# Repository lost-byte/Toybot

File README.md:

# Toybot
Simple wheel robot with programming terminal pickaback.

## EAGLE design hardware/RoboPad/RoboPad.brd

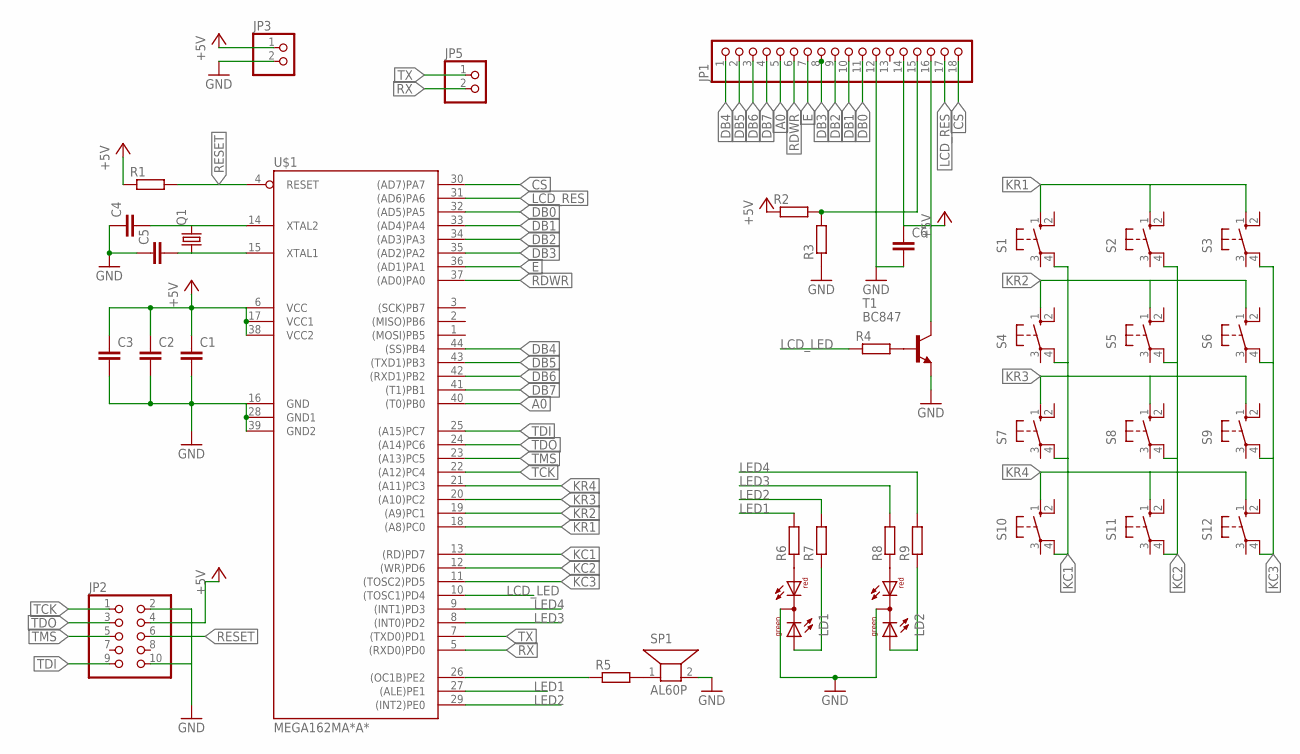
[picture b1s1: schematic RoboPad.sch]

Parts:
C1, C2, C3, C4, C5, C6: C-EUC0805; C0805
JP1: PINHD-1X18; 1X18
JP2: PINHD-2X5; 2X05
JP3, JP5: PINHD-1X2/90; 1X02/90
LD1, LD2: DUOLED-RG-C; DUOLED-C-5MM
Q1: CRYSTALHC49U-V; HC49U-V
R1, R2, R3, R4, R5, R6, R7, R8, R9: R-EU_R0805; R0805
S1, S2, S3, S4, S5, S6, S7, S8, S9, S10, S11, S12: 10-XX; B3F-10XX
SP1: AL60P
T1: BC847; SOT23
U$1: MEGA162MA*A*; TQFP44

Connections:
+5V: C1.1, C2.1, C3.1, C6.1, JP1.14, JP2.4, JP3.1, R1.1, R2.1, U$1.6 (VCC), U$1.17 (VCC1), U$1.38 (VCC2)
A0: JP1.5, U$1.40 ((T0)PB0)
CS: JP1.18, U$1.30 ((AD7)PA7)
DB0: JP1.11, U$1.32 ((AD5)PA5)
DB1: JP1.10, U$1.33 ((AD4)PA4)
DB2: JP1.9, U$1.34 ((AD3)PA3)
DB3: JP1.8, U$1.35 ((AD2)PA2)
DB4: JP1.1, U$1.44 ((SS)PB4)
DB5: JP1.2, U$1.43 ((TXD1)PB3)
DB6: JP1.3, U$1.42 ((RXD1)PB2)
DB7: JP1.4, U$1.41 ((T1)PB1)
E: JP1.7, U$1.36 ((AD1)PA1)
GND: C1.2, C2.2, C3.2, C4.1, C5.1, C6.2, JP1.12, JP2.2, JP2.10, JP3.2, LD1.C, LD2.C, R3.1, SP1.2, T1.2 (E), U$1.16 (GND), U$1.28 (GND1), U$1.39 (GND2)
KC1: S1.4 (P1), S4.4 (P1), S7.4 (P1), S10.4 (P1), U$1.13 ((RD)PD7)
KC2: S2.4 (P1), S5.4 (P1), S8.4 (P1), S11.4 (P1), U$1.12 ((WR)PD6)
KC3: S3.4 (P1), S6.4 (P1), S9.4 (P1), S12.4 (P1), U$1.11 ((TOSC2)PD5)
KR1: S1.1 (S), S2.1 (S), S3.1 (S), U$1.18 ((A8)PC0)
KR2: S4.1 (S), S5.1 (S), S6.1 (S), U$1.19 ((A9)PC1)
KR3: S7.1 (S), S8.1 (S), S9.1 (S), U$1.20 ((A10)PC2)
KR4: S10.1 (S), S11.1 (S), S12.1 (S), U$1.21 ((A11)PC3)
LCD_LED: R4.1, U$1.10 ((TOSC1)PD4)
LCD_RES: JP1.17, U$1.31 ((AD6)PA6)
LED1: R6.2, U$1.27 ((ALE)PE1)
LED2: R7.2, U$1.29 ((INT2)PE0)
LED3: R8.2, U$1.8 ((INT0)PD2)
LED4: R9.2, U$1.9 ((INT1)PD3)
unnamed: C4.2, Q1.2, U$1.14 (XTAL2)
unnamed: C5.2, Q1.1, U$1.15 (XTAL1)
unnamed: JP1.16, T1.3 (C)
unnamed: JP1.15, R2.2, R3.2
unnamed: R5.1, U$1.26 ((OC1B)PE2)
unnamed: R5.2, SP1.1
unnamed: R4.2, T1.1 (B)
unnamed: LD1.AR, R6.1
unnamed: LD2.AR, R8.1
unnamed: LD1.AX (AG), R7.1
unnamed: LD2.AX (AG), R9.1
RDWR: JP1.6, U$1.37 ((AD0)PA0)
RESET: JP2.6, R1.2, U$1.4 (RESET)
RX: JP5.2, U$1.5 ((RXD0)PD0)
TCK: JP2.1, U$1.22 ((A12)PC4)
TDI: JP2.9, U$1.25 ((A15)PC7)
TDO: JP2.3, U$1.24 ((A14)PC6)
TMS: JP2.5, U$1.23 ((A13)PC5)
TX: JP5.1, U$1.7 ((TXD0)PD1)

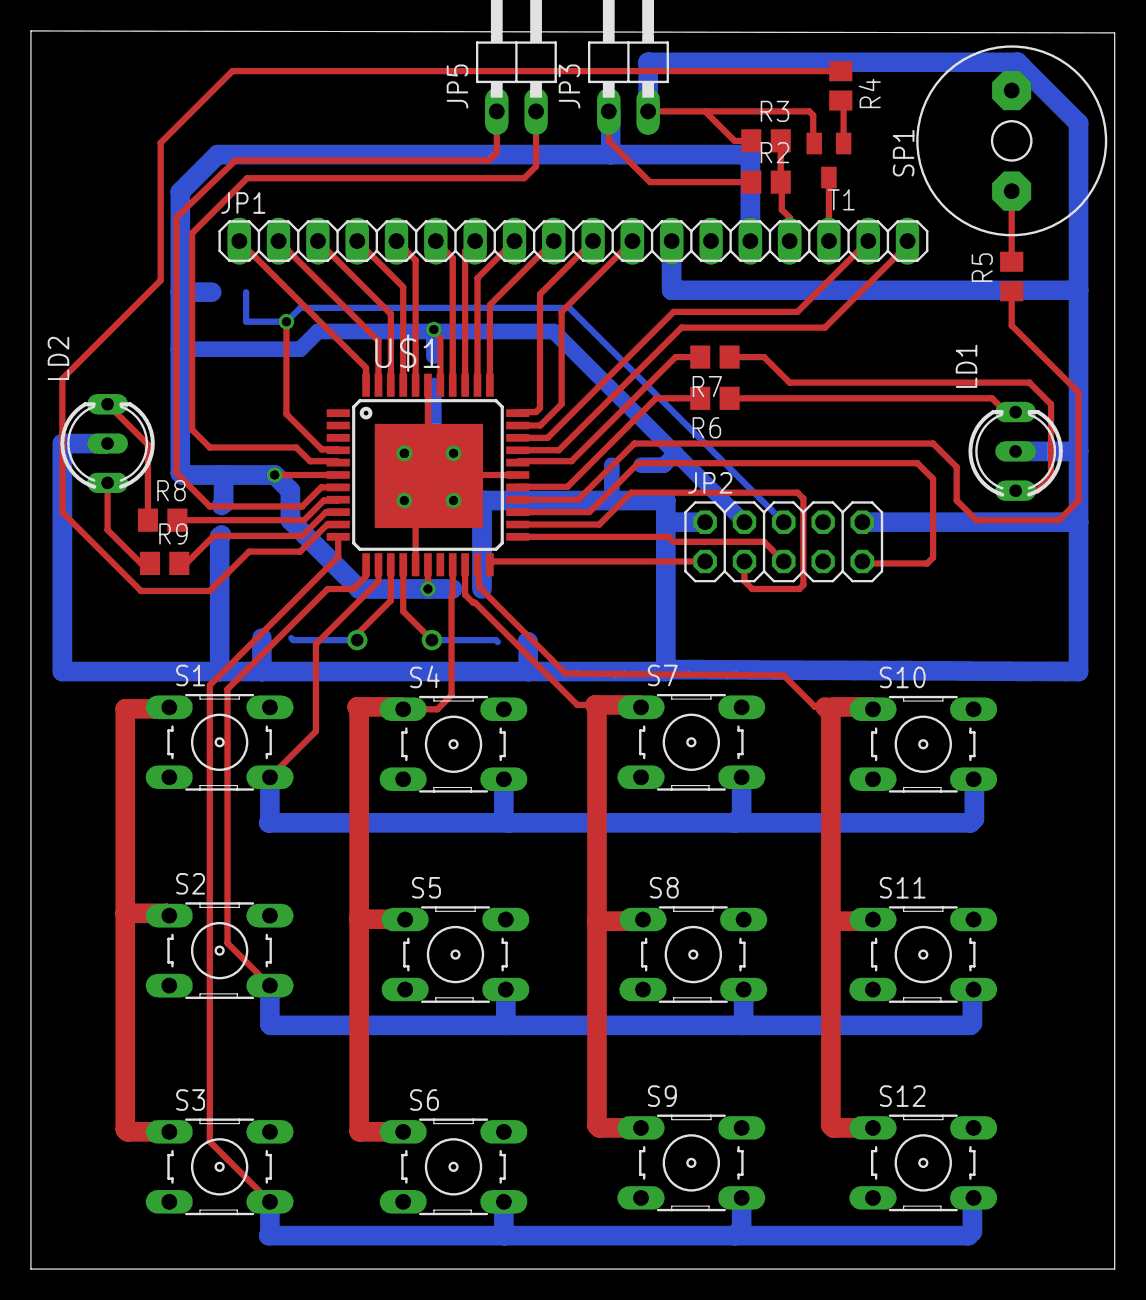
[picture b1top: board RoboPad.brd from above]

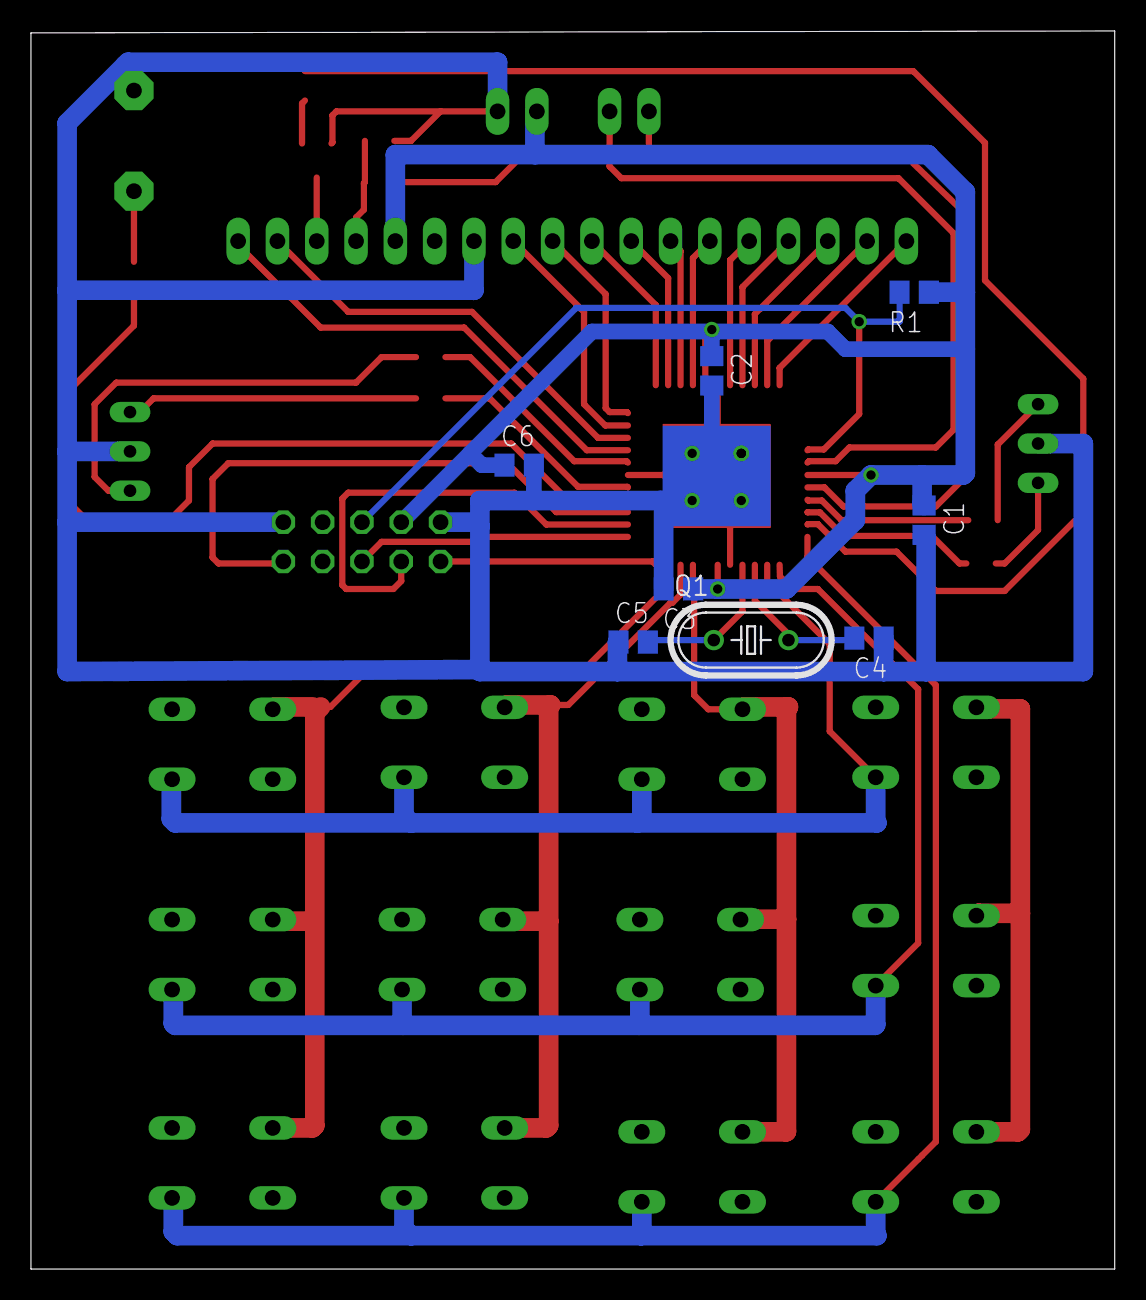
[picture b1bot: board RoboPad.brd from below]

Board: 2 copper layers, 70.0 x 80.0 mm, 37 parts (8 on the bottom side), 45 nets.

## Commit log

2018-12-26 Create platform.ino
    There are interpreter, cli and editor. It's works! Not bad for first commit.
2018-12-26 Control console PCB design added
    Control console PCB design added
2018-12-26 Started RoboPad code
    Started RoboPad code. LCD will be driven by olikraus/u8g2 library
2018-12-28 C project grows
2018-12-29 Tryeing to start LCD
2019-01-09 LCD code fighting
2019-01-11 Done LCD base code
2019-01-11 Fix folder structure
2019-01-11 Folder Name
2019-01-14 Editor code started
2019-01-14 Go on Editor
2019-01-15 Changed editor gliphs
2019-01-16 Code list started
2019-01-24 Grous up
2019-01-25 going futher
2019-01-29 going on
